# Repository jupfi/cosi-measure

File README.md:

# COSI Measure

<!-- TOC -->

- [COSI Measure](#cosi-measure)
  - [Description](#description)
  - [System specifications](#system-specifications)
  - [Versions and Branches](#versions-and-branches)
  - [Contacts](#contacts)
    - [Known builds](#known-builds)
  - [Contributors alphabetical order](#contributors-alphabetical-order)
  - [Publications](#publications)
  - [Acknowledgments](#acknowledgments)
  - [License and Liability](#license-and-liability)

<!-- /TOC -->
## Description

COSI Measure is an open source multipurpose 3-axis robot operating in a large volume, that can be equipped with e.g. field mapping probes for static or dynamic field measurements (electromagnetic, temperature etc.). Submillimeter fidelity and reproducibility/backlash performance were evaluated experimentally. It can be potentially upgraded to be used as a CNC, for 3D printing or other applications, that require reproducible submillimeter movements.

## System specifications

- Dimension: (80x90x105)cm³
- Working volume: (53x53x64)cm³
- Precision: positioning error <1mm
- Max load: ~20kg
- Applied force: 896N (91kg)
- Standalone system
- Inductive limit switches
- Emergency Stop
- Open Source Software GUI (Python)
- Estimated material costs: ~2000€

More photos and videos can be found on opensourceimaging.org: <https://www.opensourceimaging.org/project/cosi-measure/>

## Versions and Branches

You're currently viewing the `main` branch, showing ongoing development on `v2.0.*` of the COSI Measure system.\
New versions are developed in dedicated feature branches and then merged here.

The latest stable release is [v2.0](https://github.com/opensourceimaging/cosi-measure/releases/tag/v2.0).

For older, please check out the [releases overview](https://github.com/opensourceimaging/cosi-measure/releases/).

The changes between versions are summarized in the respective release notes and documented in the [CHANGELOG](CHANGELOG.md) document.

## Contacts

General contact:
Name | Email | Institution | COSI Measure Applications
-----|-----|-----|-----|
Lukas Winter | <lukas.winter@ptb.de> | Physikalisch-Technische Bundesanstalt (PTB), Berlin, Germany | Magnetic field mapping of MR magnets, implant safety measurements, RF field mapping of RF coils using time-domain H- and E-field sensors, Measurements within an MR scanner, 3D printing

### (Known) builds

Name | Email | Institution | COSI Measure Applications
-----|-----|-----|-----|
Haopeng Han | <haopeng.han@mdc-berlin.de> | Max-Delbrück Center for Molecular Medicine, Berlin, Germany | Temperature and RF field mapping of RF coils
Tom O'Reilly | <t.o_reilly@lumc.nl> | Leiden University Medical Center (LUMC), Leiden, Netherlands | Magnetic field mapping of low field MR magnets
Benjamin Menküc | <benjamin.menkuec@fh-dortmund.de> | University of Applied Sciences, Dortmund, Germany | Magnetic field mapping of low field MR magnets
Mark Bason | <M.Bason@sussex.ac.uk> | Quantum Systems and Devices, University of Sussex, Falmer, England | Magnetic field measurements
Wolfgang Kilian | <Wolfgang.Kilian@ptb.de> | Physikalisch-Technische Bundesanstalt (PTB), Berlin, Germany | 3D printing of phantoms

## Contributors (alphabetical order)

Nils Allek, Mark Bason, Jan Gregor Frintz, Haopeng Han, Amjad Kasabashy, Wolfgang Kilian, Ilia Kulikov, Benjamin Menküc, Tobias Mohr, Reiner Montag, Tom O'Reilly, David Shiers, Berk Silemek, Karl Stupic, Lukas Winter

## Publications

If you find this useful in your work, please cite:
[H. Han, R. Moritz, E. Oberacker, H. Waiczies, T. Niendorf and L. Winter, "Open Source 3D Multipurpose Measurement System with Submillimetre Fidelity and First Application in Magnetic Resonance", Scientific Reports, 7:13452, 2017](https://nature.com/articles/s41598-017-13824-z)

## Acknowledgments

This work is supported by the Open Source Imaging Initiative (OSI²), <https://www.opensourceimaging.org/project/cosi-measure/>

The project (21NRM05) has received funding from the European Partnership on Metrology, co-financed by the European Union's Horizon Europe Research and Innovation Programme and by the Participating States.

## License and Liability

The content in this repository is licensed under the CERN Open Hardware Licence Version 2 - Weakly Reciprocal, please see [LICENSE](LICENSE) for details and also check the [DISCLAIMER](DISCLAIMER.pdf)

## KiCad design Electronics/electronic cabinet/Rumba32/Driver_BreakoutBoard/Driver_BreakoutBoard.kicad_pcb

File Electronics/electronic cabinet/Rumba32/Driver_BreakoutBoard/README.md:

# Driver Breakout Board

<!-- TOC -->

- [Driver Breakout Board](#driver-breakout-board)
  - [Enable Logic](#enable-logic)
  - [Schematic](#schematic)
  - [BOM](#bom)
  - [Setting jumpers on Rumba32](#setting-jumpers-on-rumba32)
    - [STEPPER_DRIVER_LOGIC JUMPER](#stepper_driver_logic-jumper)
    - [Additional Software Enable Jumpers](#additional-software-enable-jumpers)

<!-- /TOC -->

This breakoutboard can be placed to the motor driver slots into the Rumba32 board.
It is useful for wiring the step, direction and enable pins via the motor connector to external motor drivers. In addition it supports an easy way of integrating a drive-enable functionality.

## Enable Logic

There can be current on the drives, if

- The Firmware enables the drives and
- some control pins are low (further explanation below) and
- Emergency Stop Relais provides it's NPN-ok signal ($0 \ V$).
- Contactor -Q1 is closed (no safe-torque-off)

Many 3D-printing firmwares are not designed for switching off the drives completely while executing a G-code file. But COSI-Measure is meant to perform magnetic measurements, so it must not disturb the measurements with noisy motor currents while performing a measurement.

A convenient workaround for Klipper is to switch on and off some extra GPIO Pins, that are wired to the hardware-enable-logic. In case you are doing something different and you do not need this feature, feel free to ignore it. Default of these Pins is low, which is also the enabled state. For details about it see the [printer.cfg](../../../software/backend/printer.cfg) file line 275-317. The drives can be enabled and disabled with g-code macros while keeping the homing active.

The NPN-ok-signal from the emergency stop relais can be daisy-chained with standard 2.54 mm jumpers to the next breakout board.

The enable input of the motordriver is not meant for a safe-torque-off function (emergency stop). Safe-torque-off is implemented in hardware (mechanical relais, contactors etc.), see [schematics](../../schematics/README.md#emergencystop).
Anyway, to prevent driver malfunction the driver will be disabled with semiconductor only circuits before the power supply of the driver will be disconnected. The delay is coming from the slower reaction of mechanical contactors and relais, so no dedicated timing module is needed.

## Schematic

## BOM

This Bill-of-Materials is for 1 breakout board only. You need one breakout board for each motor with external motor drivers, usually 3 in total (depending to your setup).

| #  | Designator | Quantity | Comment              | Man. Part-No       | Link                                                                                            |
|----|------------|----------|----------------------|--------------------|-------------------------------------------------------------------------------------------------|
| 1  | C1         | 1        | 10 nF, 0805          | C0805C103K2RECAUTO | <https://www.digikey.de/de/products/detail/kemet/C0805C103K2RECAUTO/8646745>                    |
| 2  | D1         | 1        | Dual LED red/green   | AAA3528ESGCT       | <https://www.digikey.de/de/products/detail/kingbright/AAA3528ESGCT/7318936>                     |
| 3  | IC1        | 1        | OR-Gate              | SN74ACT32PWR       | <https://www.digikey.de/en/products/detail/texas-instruments/SN74ACT32PWR/376063>               |
| 4  | J1, J2     | 2        | 8 pin header 2.54    | 61300811121        | <https://www.digikey.de/de/products/detail/w%C3%BCrth-elektronik/61300811121/4846839>           |
| 5  | J3, J5     | 2        | 2 pin header 2.54    | 61300211121        | <https://www.digikey.de/de/products/detail/w%C3%BCrth-elektronik/61300211121/4846823>           |
| 6  | J4         | 1        | 2 pos screw terminal | 0393570002         | <https://www.digikey.de/de/products/detail/molex/0393570002/946543>                             |
| 7  | Q1         | 1        | NPN Transistor       | MMBT3904           | <https://www.digikey.de/de/products/detail/micro-commercial-co/MMBT3904-TP/717280>              |
| 8  | R1         | 1        | 47 kOhm, 0805        | WR08X473 JTL       | <https://www.digikey.de/de/products/detail/walsin-technology-corporation/WR08X473-JTL/13240617> |
| 9  | R2         | 1        | 270 Ohm, 0805        | RMCF0805JT270R     | <https://www.digikey.de/de/products/detail/stackpole-electronics-inc/RMCF0805JT270R/1757887>    |
| 10  | R3, R5    | 2        | 200 Ohm, 0805        | RMCF0805FT200R     | <https://www.digikey.de/de/products/detail/stackpole-electronics-inc/RMCF0805FT200R/1760343>    |
| 11 | R4         | 1        | 1.2 kOhm, 0805       | RMCF0805JT1K20     | <https://www.digikey.de/de/products/detail/stackpole-electronics-inc/RMCF0805JT1K20/1757811>    |
| 12 | -          | 3        | 2.54 mm jumper       | QPC02SXGN-RC       | <https://www.digikey.de/en/products/detail/sullins-connector-solutions/QPC02SXGN-RC/2618262>    |

## Setting jumpers on Rumba32

### STEPPER_DRIVER_LOGIC JUMPER

The STEPPER_DRIVER_LOGIC jumper (see picture below) selects the logic voltage supplied to all stepper driver
sockets. By default, it is configured so that 3.3V is supplied to the stepper drivers. However, since the external motor drivers need 5 V, the track between the centre and 3V pad should be cut, and a solder joint placed over the 5V and centre pad. <br>
 <br>
(picture and parts of the text above borrowed from <https://github.com/Aus3D/RUMBA32/blob/master/Resources/Manual/RUMBA32%20V1.1%20User%20Manual%20-%20REV%20A.pdf>, License: GPLv2)

### Additional Software Enable Jumpers

Set the jumpers beneath the breakoutboards as seen in the picture below (blue):

 <br>
(Picture borrowed and modified from <https://github.com/Aus3D/RUMBA32?tab=readme-ov-file>, License: GPLv2)

These jumpers are connecting some GPIO-Pins to the enable logic of this breakout board.

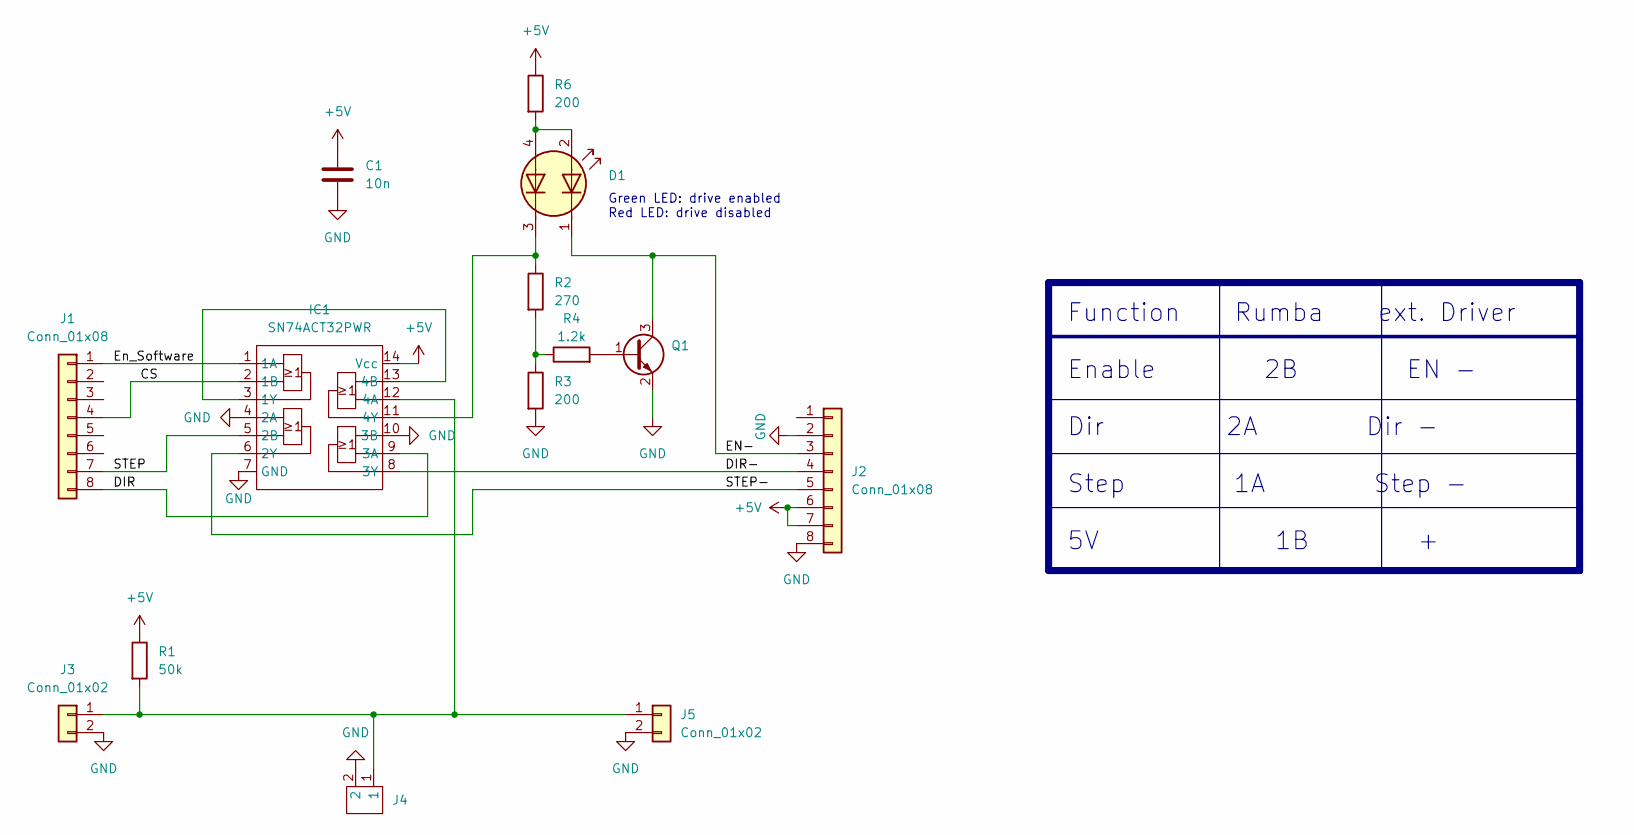
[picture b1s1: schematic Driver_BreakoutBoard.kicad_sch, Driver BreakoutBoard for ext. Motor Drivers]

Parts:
C1: 10n; C_0805_2012Metric_Pad1.18x1.45mm_HandSolder
D1: LED_Dual; LED_Kingbright_AAA3528ESGCT
IC1: SN74ACT32PWR; SOT402-1_NXP-M
J1, J2: Conn_01x08; PinHeader_1x08_P2.54mm_Vertical
J3, J5: Conn_01x02; PinHeader_1x02_P2.54mm_Vertical
J4: 0393570002
Q1: Q_NPN_CEB; SOT-23_Handsoldering
R1: 50k; R_0805_2012Metric_Pad1.20x1.40mm_HandSolder
R2: 270; R_0805_2012Metric_Pad1.20x1.40mm_HandSolder
R3, R6: 200; R_0805_2012Metric_Pad1.20x1.40mm_HandSolder
R4: 1.2k; R_0805_2012Metric_Pad1.20x1.40mm_HandSolder

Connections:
+5V: C1.1, IC1.14 (Vcc), J2.6, J2.7, R1.1, R6.1
/CS: IC1.2 (1B), J1.4
/DIR: IC1.9 (3A), J1.8
/DIR-: IC1.8 (3Y), J2.4
/EN-: D1.1 (A1), J2.3, Q1.3 (C)
/En_Software: IC1.1 (1A), J1.1
/STEP: IC1.5 (2B), J1.7
/STEP-: IC1.6 (2Y), J2.5
GND: C1.2, IC1.4 (2A), IC1.7 (GND), IC1.10 (3B), J2.2, J2.8, J3.2, J4.2, J5.2, Q1.2 (E), R3.2
unnamed: D1.2 (K1), D1.4 (K2), R6.2
unnamed: D1.3 (A2), IC1.11 (4Y), R2.1
unnamed: IC1.12 (4A), J3.1, J4.1, J5.1, R1.2
unnamed: IC1.3 (1Y), IC1.13 (4B)
unnamed: Q1.1 (B), R4.2
unnamed: R2.2, R3.1, R4.1

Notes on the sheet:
Function Rumba ext. Driver Enable 2B EN - Dir 2A Dir - Step 1A Step - 5V 1B +
Green LED: drive enabled Red LED: drive disabled

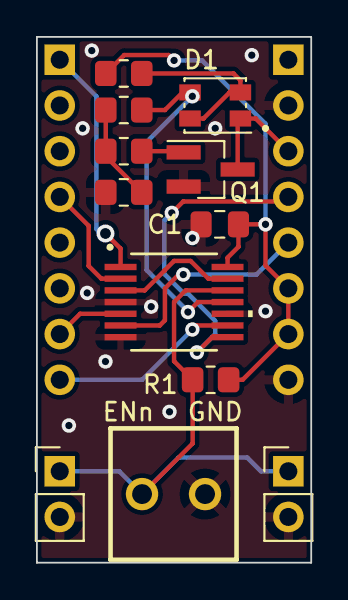
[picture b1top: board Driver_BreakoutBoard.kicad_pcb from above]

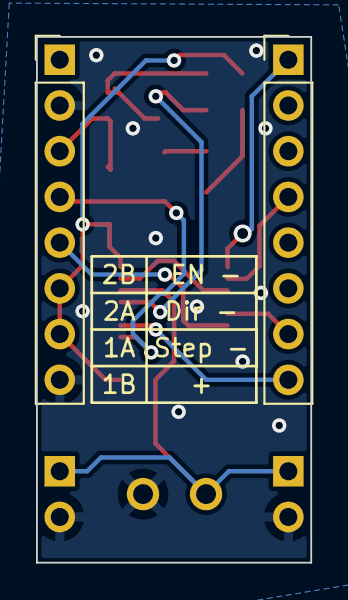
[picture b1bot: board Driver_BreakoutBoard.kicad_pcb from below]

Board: 2 copper layers, 15.2 x 29.2 mm, 14 parts (2 on the bottom side), 15 nets.

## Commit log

2024-07-12 Fixed link for pe cage clamp.
2024-07-12 Added requirements.txt and instructions on how to install the GUI.
2024-07-12 Note about installation in venv.
2024-07-23 Prelim. schematic updates.
2024-07-23 Fixed F2 symbol.
2024-07-23 Fixed wrong bridge.
2024-07-23 Formatting.
2024-07-29 Fixed mistakes in X1 wiring table.
2024-07-29 Updated PowerSupply schematic.
2024-07-29 Added notes about safety-relays settings.
2024-07-29 Formatting, typos.
2024-08-01 Changed safety relays function to correct one.
2024-08-03 Added Markdown BoM.
2024-08-04 Fixed mistake in mech BoM.
2024-08-29 Updated with new PCB Layout.
2024-08-29 Small improvement to board layout.
2024-08-29 Updated changelog.
2024-08-30 Fixed requirement.
2024-08-30 Started moonraker implementation.
2024-09-02 Updated enable logic to work with the breakoutboards.
2024-09-02 Updated terminal plan
2024-09-02 Added mechanical build instructions.
2024-09-02 Updated electrical BoM.
2024-09-02 Updated electrical assembly instructions.
2024-09-02 Added some more pictures.
2024-09-03 Removed old assembly instructions.
2024-09-03 Updated directory structure.
2024-09-03 Typo.
2025-03-14 Fixed issue with loss of firmware.
